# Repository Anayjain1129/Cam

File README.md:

# ESP-Camera
Okay so this is basically a hand held camera that you can use to capture pictures and as per the name yes it uses ESP32 S3 to make the work happen! It has two parts one transmitter and one receiver so yea! u can capture pictures with the transmitter and then just wirelessly export the picture from the receiver but i have made the case like u can use both of them in a single case but yea! u can just use it wirelessly too! so yea! 

# Why did i made this?
i do have a camera that i bought from shenzhen china yes i went to fallout but i always wanted to make my own handheld camera and also i have to complete my horizons hours for stipend so im just making stuff that i wanted to make! 

# What was the hardest part?
the part which was really hard was reading the datasheet i mean like vro what were those

# Features:
- Uses ESP32
- Unique Design
- Wireless Image sharing
- Compact Design

# What about Firmware? 
so for firmware i have just upload a very simple structural code cause like it's not really possible to write code for project without having the physical hardware of the project in the hands so yea! 

# Images-

# Schematics

# PCB

# CAD

# BOM

| Item | Qty | Price (USD) | Source |
|---|---|---|---|
| ESP32-S3 (Seeed XIAO Sense) | 1 | $25.40 | [Robodo](https://robodo.in/products/seeed-studio-xiao-esp32s3-sense-2-4ghz-wi-fi-ble-5-0-ov2640-camera-sensor-digital-microphone-battery-charge-supported-rich-interface-iot-embedded-ml?variant=44827345879240) |
| Li-ion Battery | 1 | — | Self-sourced |
| Battery holder | 1 | $1.00 | [Amazon](https://www.amazon.in/gp/product/B0D6YYMF9R/) |
| SPST Slide switch | 1 | $0.82 | [Amazon](https://www.amazon.in/gp/product/B08S6XSBBD/) |
| ESP32-S3 Super Mini | 1 | $7.30 | [Amazon](https://www.amazon.in/Autables-ESP32-S3-Supermini-Development-Bluetooth/dp/B0H8YMNKHL/) |
| 1.8" TFT display | 1 | $4.70 | [Amazon](https://www.amazon.in/ROBODUINO-Without-Screen-Module-Resolution/dp/B0H688V2MF/) |
| Micro SD Card | 1 | — | Self-sourced |
| Switches | 3 | — | Self-sourced |
| Keycaps | 3 | — | 3D printed |
| 100nF Capacitor | 1 | — | Self-sourced |
| 10nF Capacitor | 1 | — | Self-sourced |
| PCB | 5 | $13.90 | [JLCPCB](https://jlcpcb.com) |

**Total (excl. self-sourced parts): ~$53.12**

# How is case gonna be printed?
The case is gonna be printed by my Bambu Lab A1 mini

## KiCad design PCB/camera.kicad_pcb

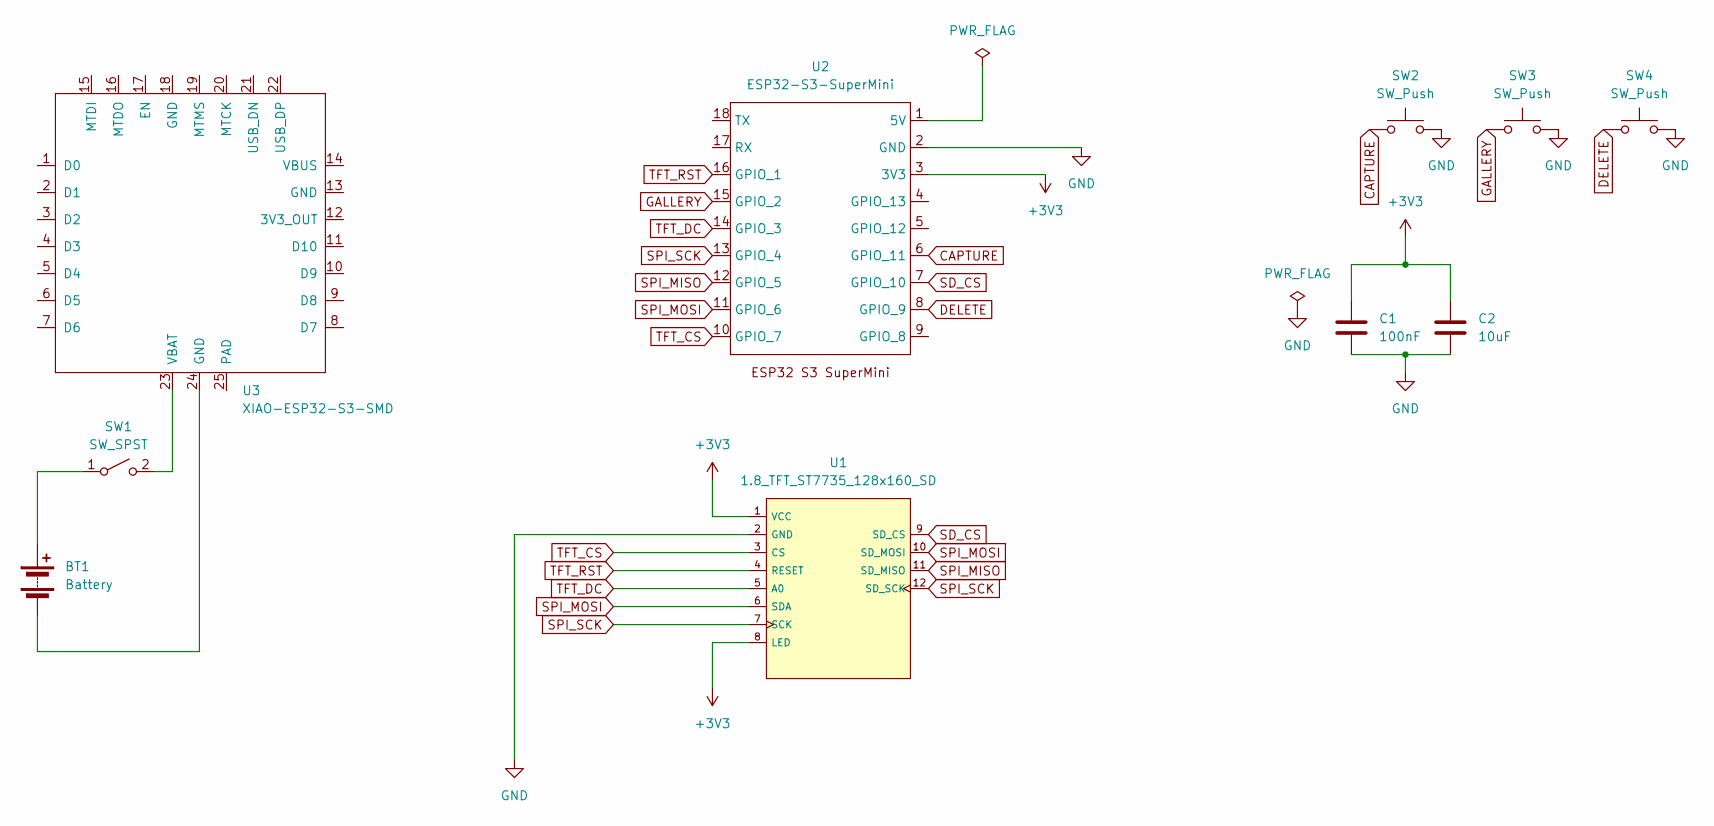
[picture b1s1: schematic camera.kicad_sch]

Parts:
BT1: Battery; BatteryHolder_Keystone_1042_1x18650
C1: 100nF; C_Disc_D5.0mm_W2.5mm_P5.00mm
C2: 10uF; CP_Radial_D5.0mm_P2.00mm
SW1: SW_SPST; PinHeader_1x02_P2.54mm_Vertical
SW2, SW3, SW4: SW_Push; SW_Cherry_MX_1.00u_PCB
U1: 1.8_TFT_ST7735_128x160_SD; TFT LCD 1.8inch 128x160 w_ SD Card Slot
U2: ESP32-S3-SuperMini
U3: XIAO-ESP32-S3-SMD

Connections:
+3V3: C1.1, C2.1, U1.1 (VCC), U1.8 (LED), U2.3 (3V3)
CAPTURE: SW2.1, U2.6 (GPIO_11)
DELETE: SW4.1, U2.8 (GPIO_9)
GALLERY: SW3.1, U2.15 (GPIO_2)
GND: C1.2, C2.2, SW2.2, SW3.2, SW4.2, U1.2 (GND), U2.2 (GND)
unnamed: BT1.1 (+), SW1.1 (A)
unnamed: BT1.2 (-), U3.24 (GND)
unnamed: SW1.2 (B), U3.23 (VBAT)
SD_CS: U1.9 (SD_CS), U2.7 (GPIO_10)
SPI_MISO: U1.11 (SD_MISO), U2.12 (GPIO_5)
SPI_MOSI: U1.6 (SDA), U1.10 (SD_MOSI), U2.11 (GPIO_6)
SPI_SCK: U1.7 (SCK), U1.12 (SD_SCK), U2.13 (GPIO_4)
TFT_CS: U1.3 (CS), U2.10 (GPIO_7)
TFT_DC: U1.5 (A0), U2.14 (GPIO_3)
TFT_RST: U1.4 (RESET), U2.16 (GPIO_1)

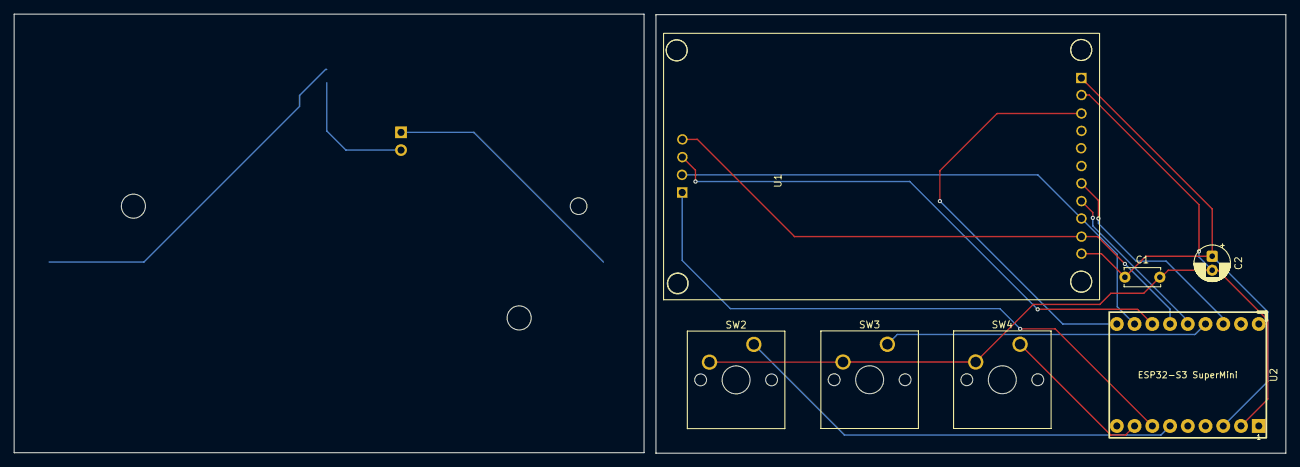
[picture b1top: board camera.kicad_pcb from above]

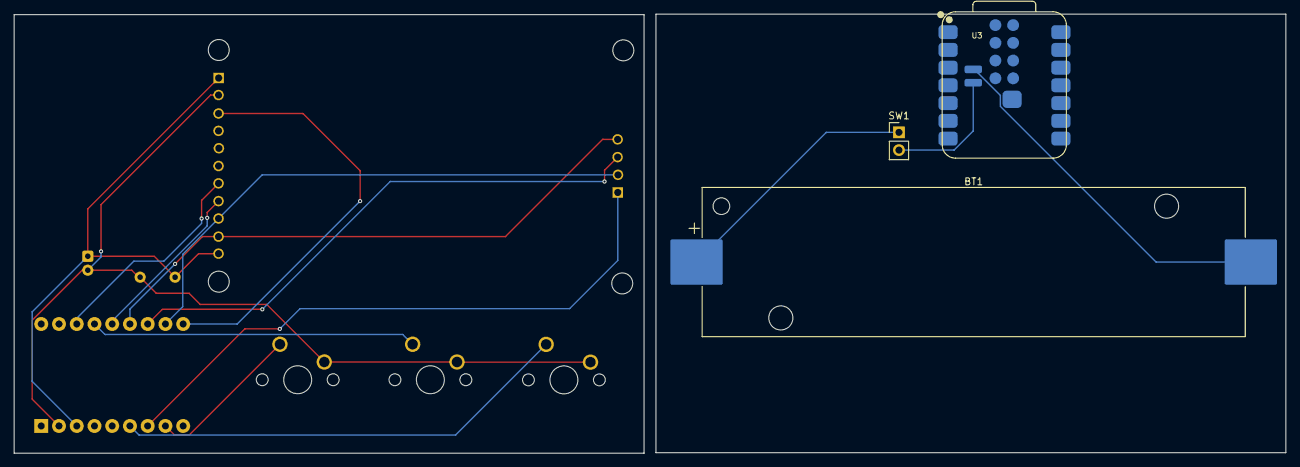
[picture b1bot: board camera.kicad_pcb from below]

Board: 2 copper layers, 182.1 x 62.9 mm, 10 parts (3 on the bottom side), 15 nets.

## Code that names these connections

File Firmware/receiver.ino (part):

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    - SD (built-in) 

  Pin map (finalized earlier in the project):
    SPI_SCK   -> GPIO4   (shared TFT + SD)
    SPI_MOSI  -> GPIO6   (shared TFT + SD)
    SPI_MISO  -> GPIO5   (SD only)
    TFT_CS    -> GPIO7
    SD_CS     -> GPIO10
    TFT_DC    -> GPIO3
    TFT_RST   -> GPIO1
    BTN_CAPTURE -> GPIO11
    BTN_GALLERY -> GPIO2
    BTN_DELETE  -> GPIO9
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const uint16_t TRANSMITTER_PORT = 80;

// ---------- Pin map ----------
#define TFT_CS    7
#define TFT_DC    3
#define TFT_RST   1
#define SD_CS     10
#define SPI_SCK   4
#define SPI_MOSI  6
#define SPI_MISO  5

#define BTN_CAPTURE 11
#define BTN_GALLERY 2
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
